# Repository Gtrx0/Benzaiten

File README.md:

# Benzaiten

## Information
Based on https://diyaudioheaven.wordpress.com/headphones/measurements/brands-s-se/hd58x-jubilee-massdrop/ schematic. The filter is supposed to decrease the treble spike at 5khz. It is supposed to make the treble sound "smoother" and "fresher" based on what diyaudioheaven says. (Never tried it myself). All credit goes to the guys behind diyaudioheaven for thinking up the filter, I just made it into a standalone pcb. They also make the kameleon amp and modules which can alter the FR even more. On another note, it would be possible
## Warning
KiCad 5 or above is needed to open this project. KiCad 4 or below won't work.

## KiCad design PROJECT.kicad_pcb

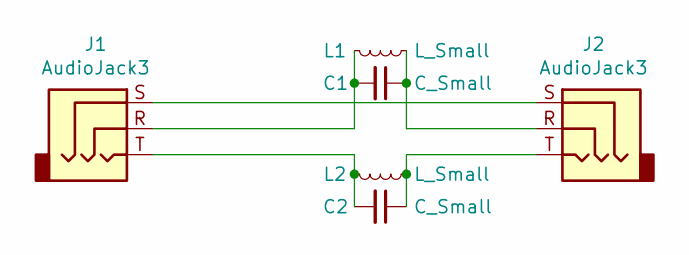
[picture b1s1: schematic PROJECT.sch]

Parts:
C1, C2: C_Small; C_Disc_D7.5mm_W5.0mm_P5.00mm
J1: AudioJack3; quarter inch TRS
J2: AudioJack3; KC-300848
L1, L2: L_Small; L_Axial_L9.5mm_D4.0mm_P15.24mm_Horizontal_Fastron_SMCC

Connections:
unnamed: C1.1, J2.R, L1.1
unnamed: C1.2, J1.R, L1.2
unnamed: C2.1, J2.T, L2.1
unnamed: C2.2, J1.T, L2.2
unnamed: J1.S, J2.S

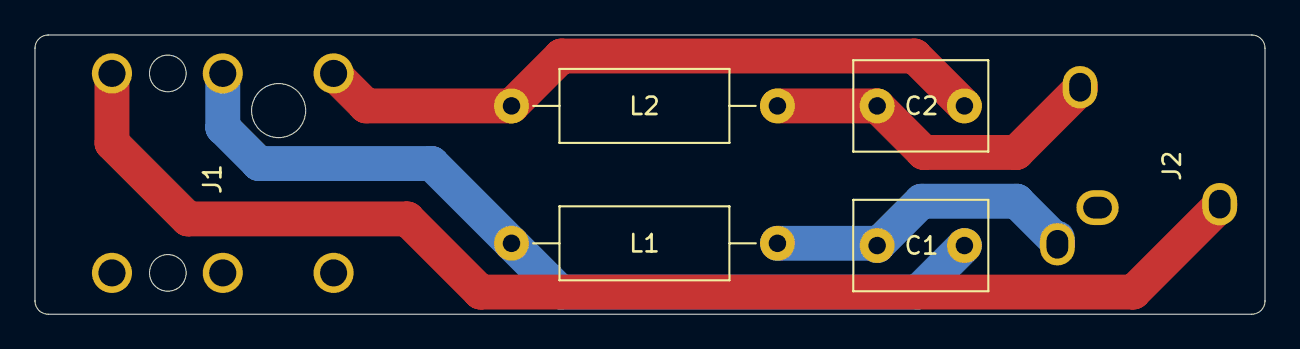
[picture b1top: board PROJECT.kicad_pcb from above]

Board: 2 copper layers, 70.5 x 16.0 mm, 6 parts (1 on the bottom side), 5 nets.

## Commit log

2019-01-03 Design
